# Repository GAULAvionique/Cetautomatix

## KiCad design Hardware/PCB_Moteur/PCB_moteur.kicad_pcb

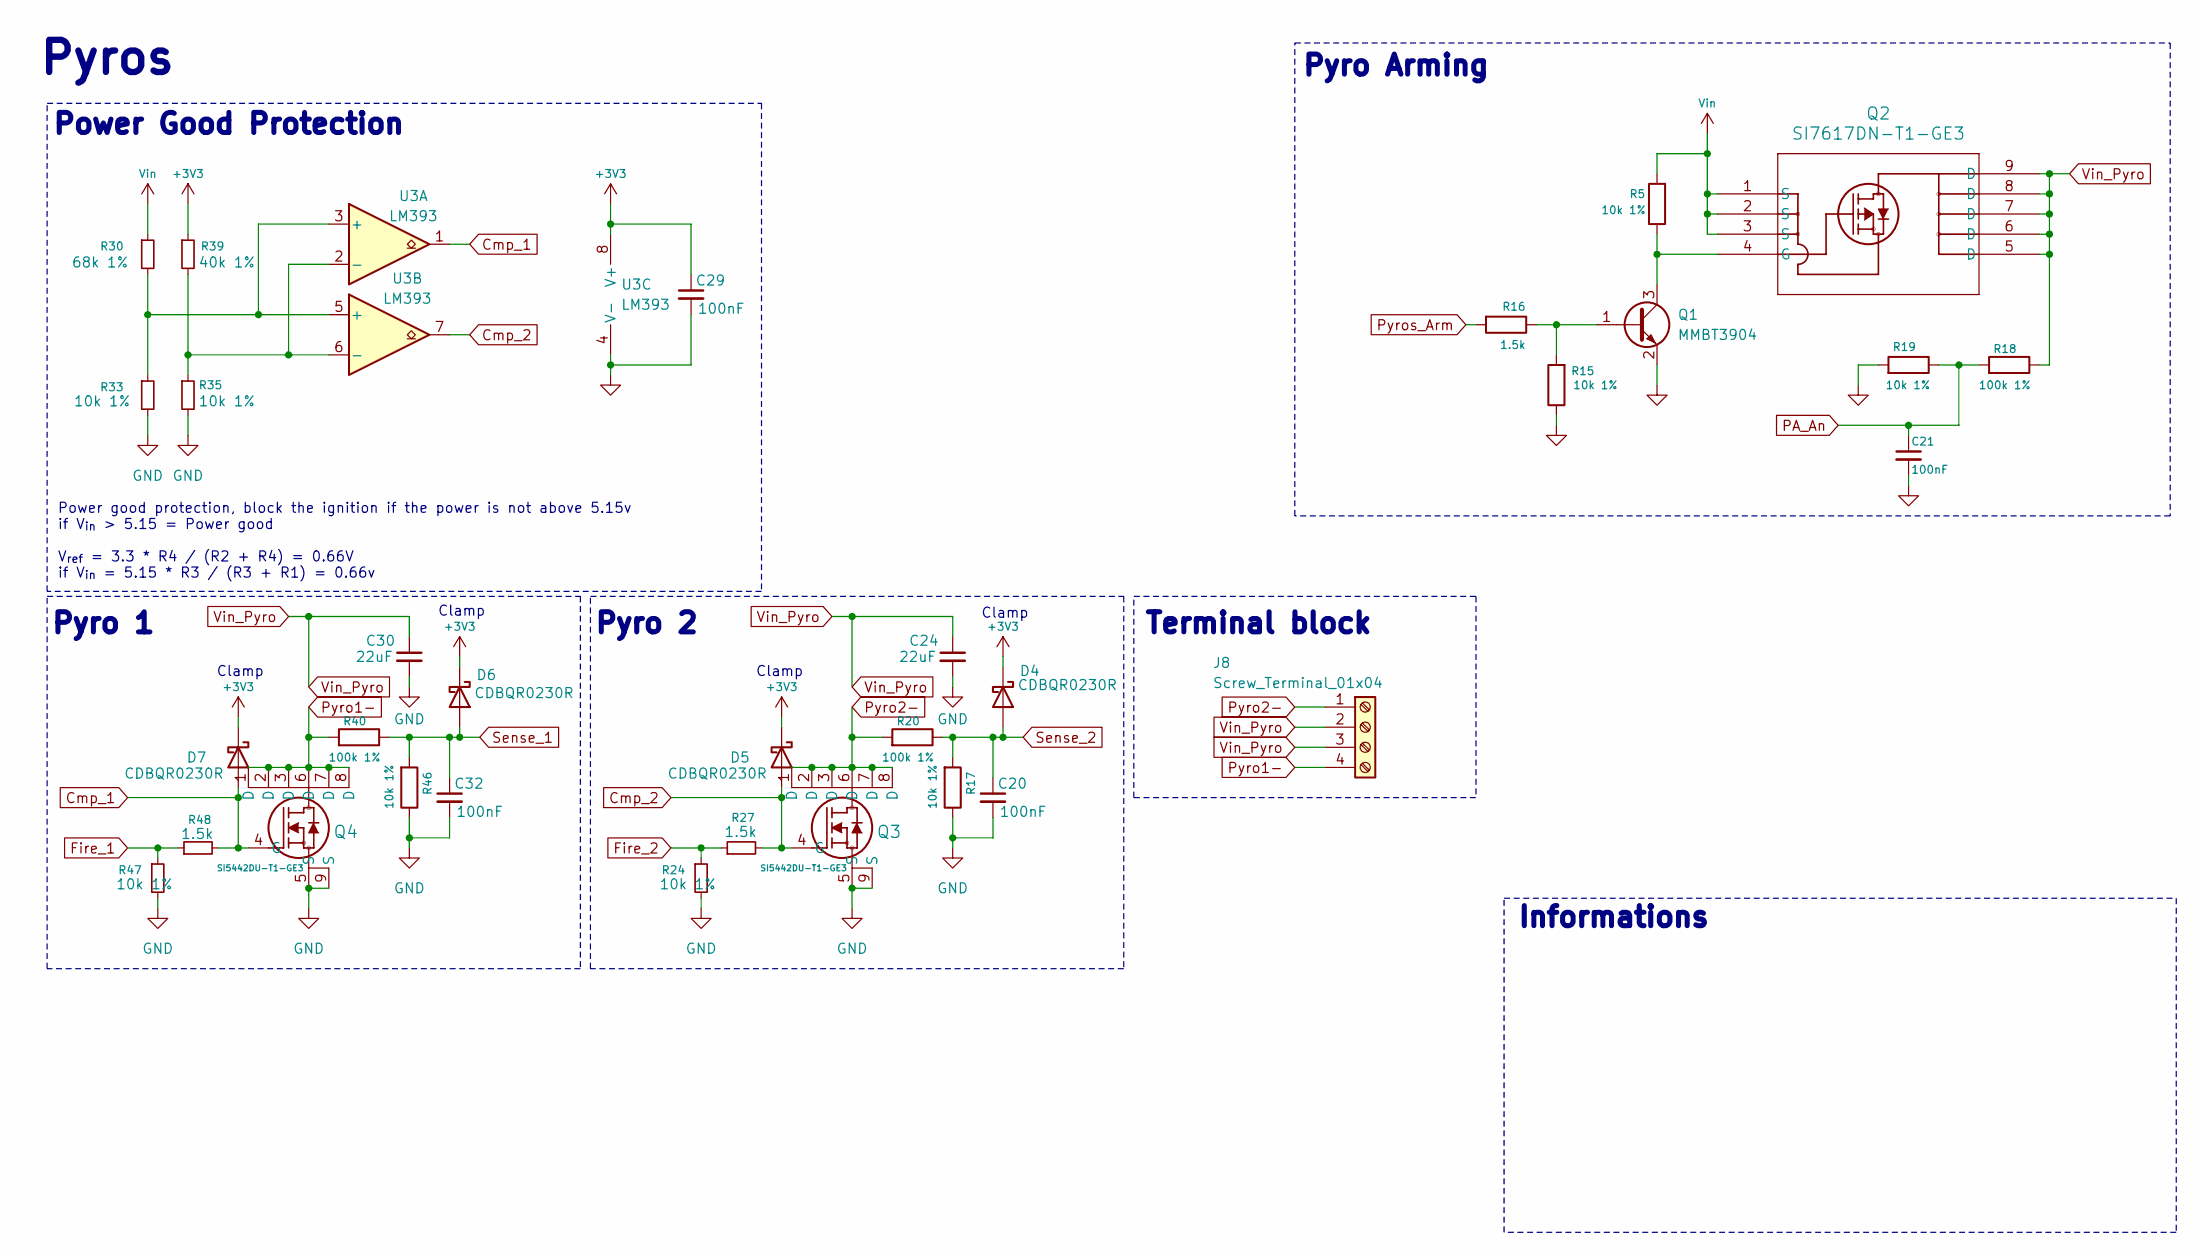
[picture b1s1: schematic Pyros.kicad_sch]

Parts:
C20, C21, C29, C32: 100nF; C_0805_2012Metric; Manufacturer_Part_Number C0805C104K5RACTU; DigiKey_Part_Number 399-C0805C104K5RACTUCT-ND
C24, C30: 22uF; C_0805_2012Metric; Manufacturer_Part_Number C2012X5R1V226M125AC; DigiKey_Part_Number 445-14428-1-ND
D4, D5, D6, D7: CDBQR0230R; D_0603_1608Metric; Manufacturer_Part_Number CD0603-B0340R; DigiKey_Part_Number CD0603-B0340RCT-ND
J8: Screw_Terminal_01x04; CONN_OSTVN04A150_OST; Manufacturer_Part_Number OSTVN04A150; DigiKey_Part_Number ED10563-ND
Q1: MMBT3904; SOT-23; Manufacturer_Part_Number MMBT3904LT1G; DigiKey_Part_Number MMBT3904LT1GOSCT-ND
Q2: SI7617DN-T1-GE3; POWERPAK_1212-8_VIS; Manufacturer_Part_Number SI7617DN-T1-GE3; DigiKey_Part_Number SI7617DN-T1-GE3CT-ND
Q3, Q4: SI5442DU-T1-GE3; SON_8DU-T1-GE3_VIS; Manufacturer_Part_Number SI5442DU-T1-GE3; DigiKey_Part_Number SI5442DU-T1-GE3CT-ND
R5, R15, R17, R19, R24, R33, R35, R46, R47: 10k 1%; R_0805_2012Metric; Manufacturer_Part_Number CRCW080510K0FKEA; DigiKey_Part_Number 541-10.0KCCT-ND
R16, R27, R48: 1.5k; R_0805_2012Metric; Manufacturer_Part_Number RC0805FR-071K5L; DigiKey_Part_Number 311-1.50KCRCT-ND
R18, R20, R40: 100k 1%; R_0805_2012Metric; Manufacturer_Part_Number RC0805FR-07100KL; DigiKey_Part_Number 311-100KCRCT-ND
R30: 68k 1%; R_0805_2012Metric; Manufacturer_Part_Number RMCF0805FT68K0; DigiKey_Part_Number RMCF0805FT68K0CT-ND
R39: 40k 1%; R_0805_2012Metric; Manufacturer_Part_Number CRCW080540K0FKEA; DigiKey_Part_Number 541-CRCW080540K0FKEACT-ND
U3: LM393; SOIC-8_3.9x4.9mm_P1.27mm; Manufacturer_Part_Number LM393DR; DigiKey_Part_Number 296-1015-1-ND

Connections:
3V3_Main: C29.1, D4.1 (K), D5.1 (K), D6.1 (K), D7.1 (K), R39.1, U3.8 (V+); also elsewhere on the board
Cmp_1: D7.2 (A), Q4.4 (G), R48.2, U3.1
Cmp_2: D5.2 (A), Q3.4 (G), R27.2, U3.7
Fire_1: R47.1, R48.1; also elsewhere on the board
Fire_2: R24.1, R27.1; also elsewhere on the board
GND: C20.2, C21.2, C24.2, C29.2, C30.2, C32.2, Q1.2 (E), Q3.5 (S), Q3.9 (S), Q4.5 (S), Q4.9 (S), R15.1, R17.1, R19.2, R24.2, R33.2, R35.2, R46.1, R47.2, U3.4 (V-); also elsewhere on the board
unnamed: Q1.1 (B), R15.2, R16.1
unnamed: Q1.3 (C), Q2.4 (G), R5.1
unnamed: R30.2, R33.1, U3.3 (+), U3.5 (+)
unnamed: R35.1, R39.2, U3.2 (-), U3.6 (-)
PA_An: C21.1, R18.2, R19.1; also elsewhere on the board
Pyro1-: J8.4, Q4.1 (D), Q4.2 (D), Q4.3 (D), Q4.6 (D), Q4.7 (D), Q4.8 (D), R40.2
Pyro2-: J8.1, Q3.1 (D), Q3.2 (D), Q3.3 (D), Q3.6 (D), Q3.7 (D), Q3.8 (D), R20.2
Pyros_Arm: R16.2; also elsewhere on the board
Sense_1: C32.1, D6.2 (A), R40.1, R46.2; also elsewhere on the board
Sense_2: C20.1, D4.2 (A), R17.2, R20.1; also elsewhere on the board
VIN_Filtered: Q2.1 (S), Q2.2 (S), Q2.3 (S), R5.2, R30.1; also elsewhere on the board
Vin_Pyro: C24.1, C30.1, J8.2, J8.3, Q2.5 (D), Q2.6 (D), Q2.7 (D), Q2.8 (D), Q2.9 (D), R18.1

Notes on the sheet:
Power good protection, block the ignition if the power is not above 5.15v if V_{in} > 5.15 = Power good V_{ref} = 3.3 * R4 / (R2 + R4) = 0.66V if V_{in} = 5.15 * R3 / (R3 + R1) = 0.66v
Clamp
Pyro 1
Terminal block
Pyro Arming
Pyros
Informations
Power Good Protection
Pyro 2

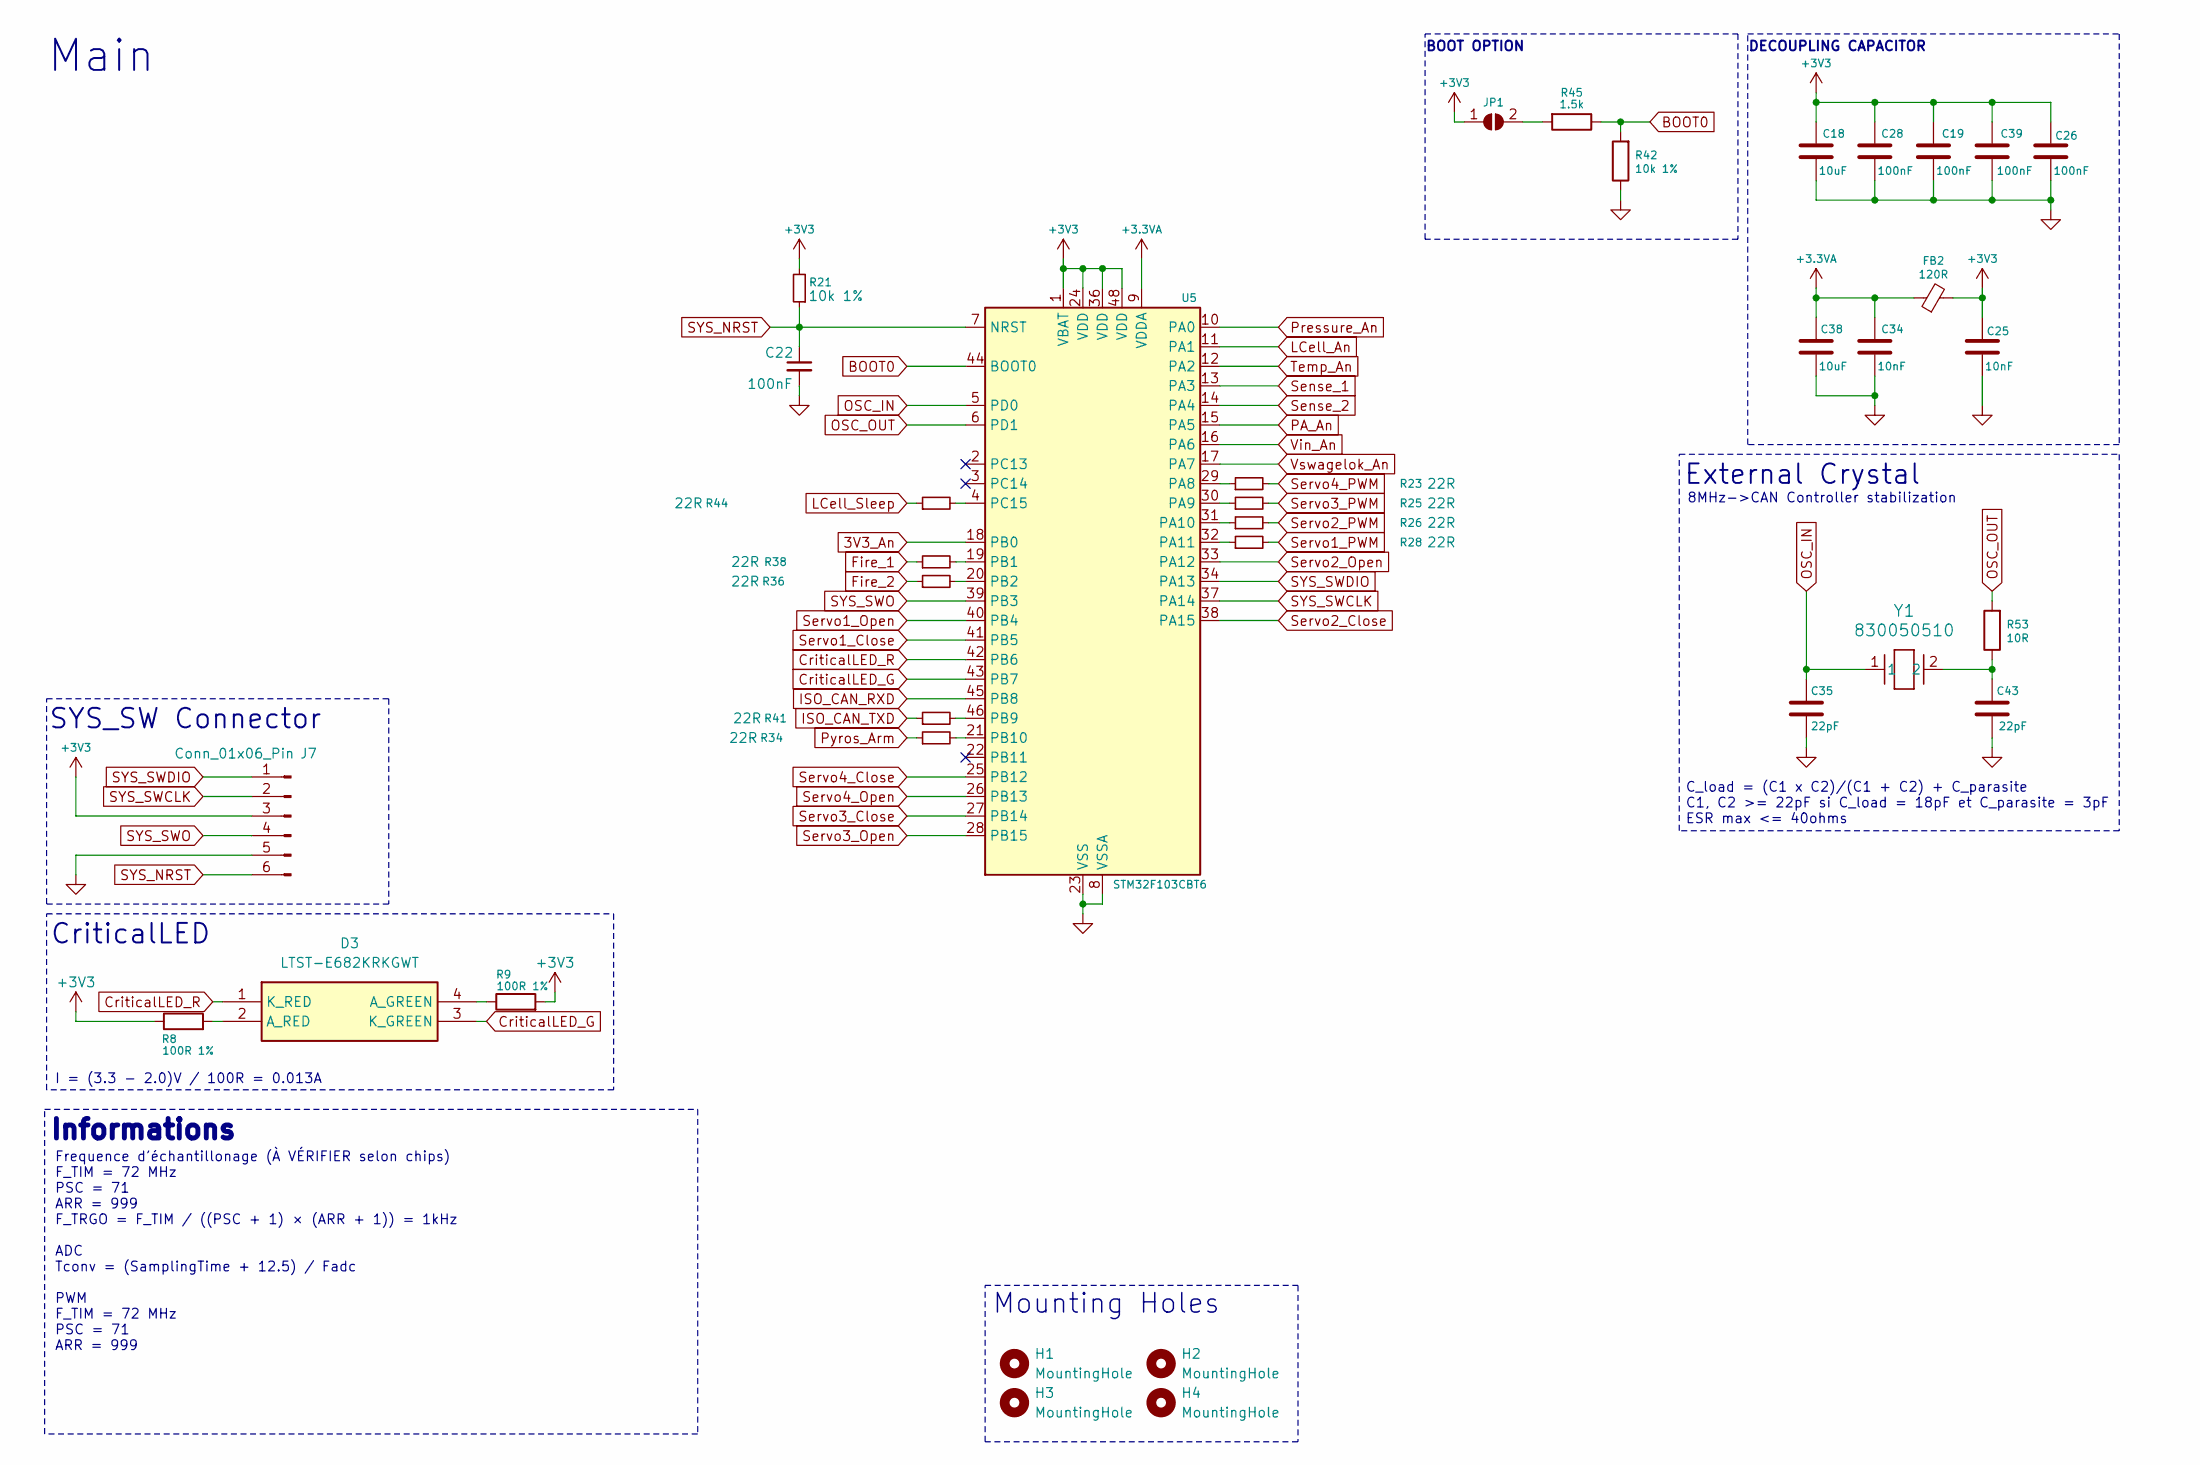
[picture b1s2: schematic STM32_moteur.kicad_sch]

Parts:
C18, C38: 10uF; C_0805_2012Metric; Manufacturer_Part_Number CL21A106KAYNNNE; DigiKey_Part_Number 1276-2891-1-ND
C19, C22, C26, C28, C39: 100nF; C_0805_2012Metric; Manufacturer_Part_Number C0805C104K5RACTU; DigiKey_Part_Number 399-C0805C104K5RACTUCT-ND
C25, C34: 10nF; C_0603_1608Metric; Manufacturer_Part_Number C0603C103K5RACTU; DigiKey_Part_Number 399-C0603C103K5RACTUCT-ND
C35, C43: 22pF; C_0805_2012Metric; Manufacturer_Part_Number QSCT251Q220F1GV001E; DigiKey_Part_Number 712-QSCT251Q220F1GV001ECT-ND
D3: LTST-E682KRKGWT; LTSTE683RGBW; Mouser Part Number 859-LTST-E682KRKGWT
FB2: 120R; L_0805_2012Metric; Manufacturer_Part_Number 2508051217Y6; DigiKey_Part_Number 1934-1472-1-ND
H1, H2, H3, H4: MountingHole; MountingHole_4.3mm_M4
J7: Conn_01x06_Pin; PinHeader_1x06_P2.54mm_Vertical; Manufacturer_Part_Number 61300611121; DigiKey_Part_Number 732-5319-ND
JP1: SolderJumper_2_Open; SolderJumper-2_P1.3mm_Open_TrianglePad1.0x1.5mm
R8, R9: 100R 1%; R_0805_2012Metric; Manufacturer_Part_Number YAG3360CT-ND; DigiKey_Part_Number RT0805FRE07100RL
R21, R42: 10k 1%; R_0805_2012Metric; Manufacturer_Part_Number CRCW080510K0FKEA; DigiKey_Part_Number 541-10.0KCCT-ND
R23, R25, R26, R28, R34, R36, R38, R41, R44: 22R; R_0603_1608Metric; Manufacturer_Part_Number ESR03EZPJ220; DigiKey_Part_Number RHM22DCT-ND
R45: 1.5k; R_0805_2012Metric; Manufacturer_Part_Number RC0805FR-071K5L; DigiKey_Part_Number 311-1.50KCRCT-ND
R53: 10R; R_0805_2012Metric; Manufacturer_Part_Number RC0805FR-0710RL; DigiKey_Part_Number 311-10.0CRCT-ND
U5: STM32F103CBT6; LQFP-48_7x7mm_P0.5mm; Manufacturer_Part_Number STM32F103CBT6; DigiKey_Part_Number 497-6288-ND
Y1: 830050510; Manufacturer_Part_Number 830050510; DigiKey_Part_Number 1923-830050510CT-ND

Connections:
3V3_An: U5.18 (PB0); also elsewhere on the board
3V3_Main: C18.2, C19.2, C25.2, C26.2, C28.2, C39.2, FB2.2, J7.3, JP1.1 (A), R8.1, R9.2, R21.2, U5.1 (VBAT), U5.24 (VDD), U5.36 (VDD), U5.48 (VDD); also elsewhere on the board
+3.3VA: C34.2, C38.2, FB2.1, U5.9 (VDDA)
BOOT0: R42.2, R45.1, U5.44 (BOOT0)
CriticalLED_G: D3.3 (K_GREEN), U5.43 (PB7)
CriticalLED_R: D3.1 (K_RED), U5.42 (PB6)
Fire_1: R38.1; also elsewhere on the board
Fire_2: R36.1; also elsewhere on the board
GND: C18.1, C19.1, C22.2, C25.1, C26.1, C28.1, C34.1, C35.1, C38.1, C39.1, C43.1, J7.5, R42.1, U5.8 (VSSA), U5.23 (VSS), U5.35 (VSS), U5.47 (VSS); also elsewhere on the board
ISO_CAN_RXD: U5.45 (PB8); also elsewhere on the board
ISO_CAN_TXD: R41.1; also elsewhere on the board
LCell_An: U5.11 (PA1); also elsewhere on the board
LCell_Sleep: R44.1; also elsewhere on the board
unnamed: C43.2, R53.1, Y1.2
unnamed: D3.4 (A_GREEN), R9.1
unnamed: D3.2 (A_RED), R8.2
unnamed: JP1.2 (B), R45.2
unnamed: R23.1, U5.29 (PA8)
unnamed: R25.1, U5.30 (PA9)
unnamed: R26.1, U5.31 (PA10)
unnamed: R28.1, U5.32 (PA11)
unnamed: R38.2, U5.19 (PB1)
unnamed: R36.2, U5.20 (PB2)
unnamed: R41.2, U5.46 (PB9)
unnamed: R34.2, U5.21 (PB10)
unnamed: R44.2, U5.4 (PC15)
OSC_IN: C35.2, U5.5 (PD0), Y1.1
OSC_OUT: R53.2, U5.6 (PD1)
PA_An: U5.15 (PA5); also elsewhere on the board
Pressure_An: U5.10 (PA0); also elsewhere on the board
Pyros_Arm: R34.1; also elsewhere on the board
SYS_NRST: C22.1, J7.6, R21.1, U5.7 (NRST)
SYS_SWCLK: J7.2, U5.37 (PA14)
SYS_SWDIO: J7.1, U5.34 (PA13)
SYS_SWO: J7.4, U5.39 (PB3)
Sense_1: U5.13 (PA3); also elsewhere on the board
Sense_2: U5.14 (PA4); also elsewhere on the board
Servo1_Close: U5.41 (PB5); also elsewhere on the board
Servo1_Open: U5.40 (PB4); also elsewhere on the board
Servo1_PWM: R28.2; also elsewhere on the board
Servo2_Close: U5.38 (PA15); also elsewhere on the board
Servo2_Open: U5.33 (PA12); also elsewhere on the board
Servo2_PWM: R26.2; also elsewhere on the board
Servo3_Close: U5.27 (PB14); also elsewhere on the board
Servo3_Open: U5.28 (PB15); also elsewhere on the board
Servo3_PWM: R25.2; also elsewhere on the board
Servo4_Close: U5.25 (PB12); also elsewhere on the board
Servo4_Open: U5.26 (PB13); also elsewhere on the board
Servo4_PWM: R23.2; also elsewhere on the board
Temp_An: U5.12 (PA2); also elsewhere on the board
Vin_An: U5.16 (PA6); also elsewhere on the board
Vswagelok_An: U5.17 (PA7); also elsewhere on the board

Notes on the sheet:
External Crystal
Mounting Holes
Main
BOOT OPTION
C_load = (C1 x C2)/(C1 + C2) + C_parasite C1, C2 >= 22pF si C_load = 18pF et C_parasite = 3pF ESR max <= 40ohms
DECOUPLING CAPACITOR
SYS_SW Connector
Informations
CriticalLED
I = (3.3 - 2.0)V / 100R = 0.013A
8MHz->CAN Controller stabilization
Frequence d'échantillonage (À VÉRIFIER selon chips) F_TIM = 72 MHz PSC = 71 ARR = 999 F_TRGO = F_TIM / ((PSC + 1) × (ARR + 1)) = 1kHz ADC Tconv = (SamplingTime + 12.5) / Fadc PWM F_TIM = 72 MHz PSC = 71 ARR = 999

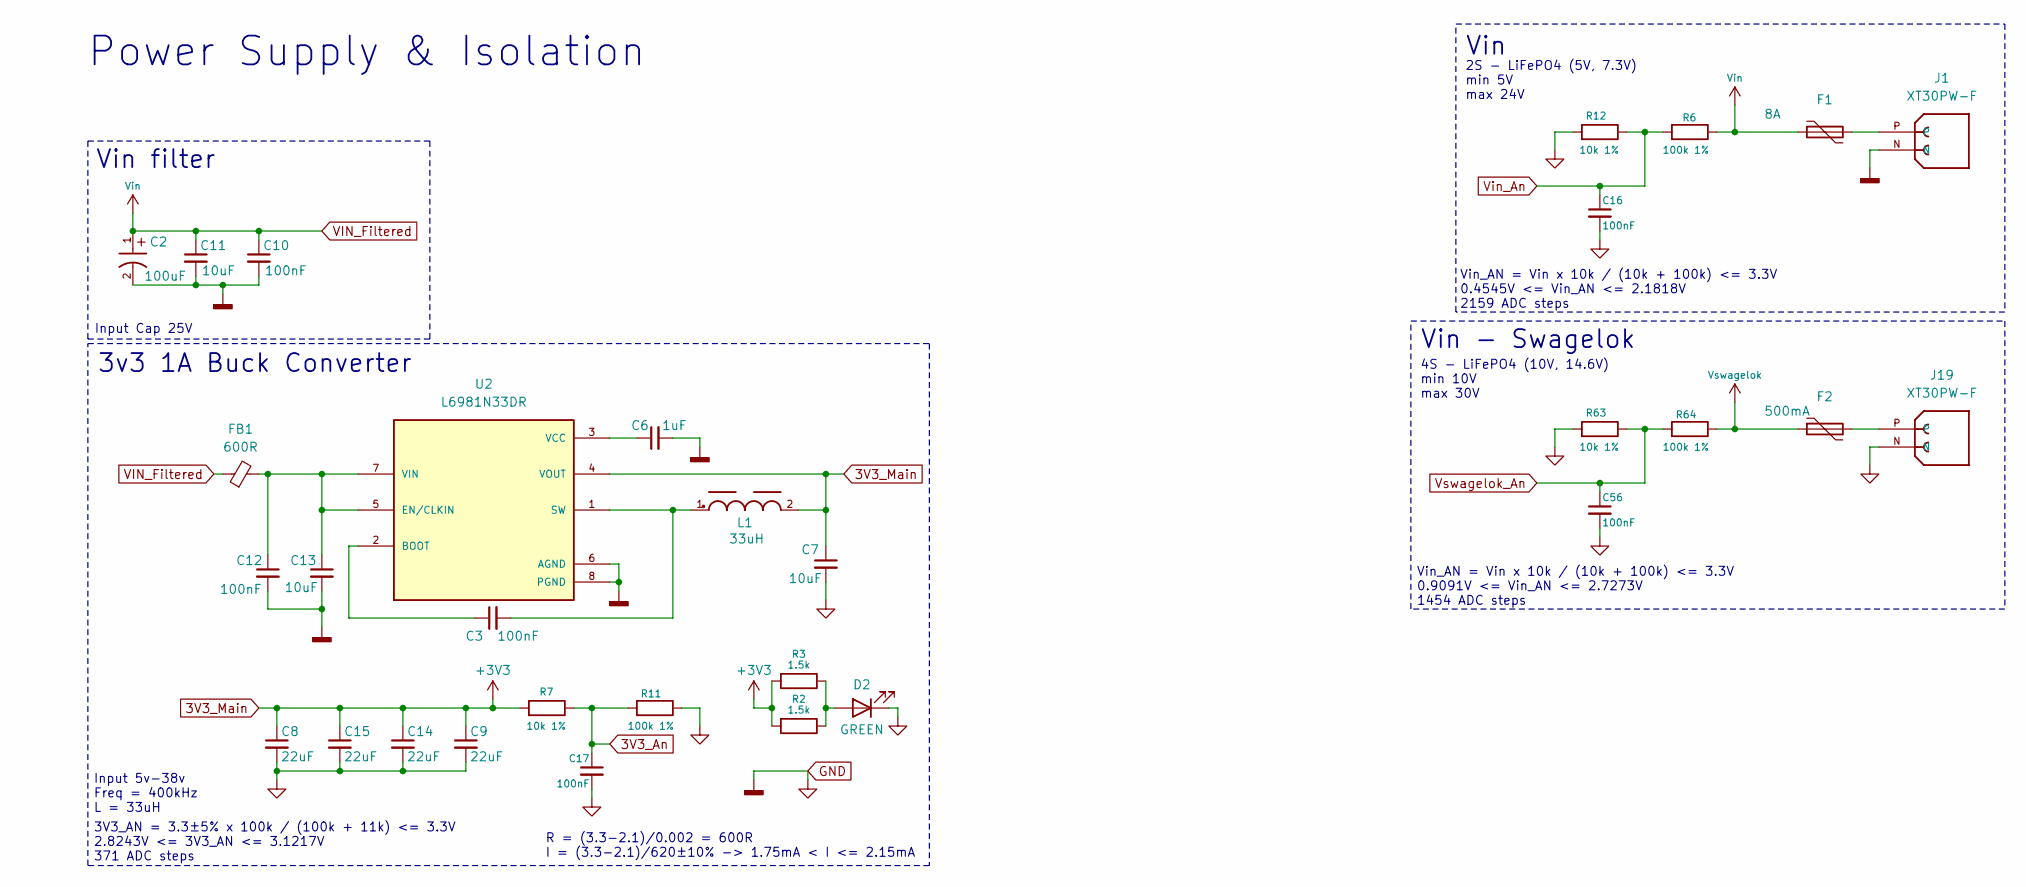
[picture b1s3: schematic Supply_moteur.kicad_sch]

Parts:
C2: 100uF; CP_Radial_D6.3mm_P2.50mm; Manufacturer_Part_Number 860040573004; DigiKey_Part_Number 732-9215-1-ND
C3, C10, C12, C16, C17, C56: 100nF; C_0805_2012Metric; Manufacturer_Part_Number C0805C104K5RACTU; DigiKey_Part_Number 399-C0805C104K5RACTUCT-ND
C6: 1uF; C_0805_2012Metric; Manufacturer_Part_Number CL21B105KBFNNNE; DigiKey_Part_Number 1276-1029-1-ND
C7, C11, C13: 10uF; C_0805_2012Metric; Manufacturer_Part_Number CL21A106KAYNNNE; DigiKey_Part_Number 1276-2891-1-ND
C8, C9, C14, C15: 22uF; C_0805_2012Metric; Manufacturer_Part_Number C2012X5R1V226M125AC; DigiKey_Part_Number 445-14428-1-ND
D2: GREEN; LED_QBLP601-AG15; Manufacturer_Part_Number QBLP601-AG15; DigiKey_Part_Number 1516-QBLP601-AG15CT-ND
F1: 8A; Fuse_2920_7451Metric; Manufacturer_Part_Number 2920L400/15MR; DigiKey_Part_Number F8136CT-ND
F2: 500mA; Fuse_0805_2012Metric; Manufacturer_Part_Number 0805L020/24YR; DigiKey_Part_Number 18-0805L020/24YRCT-ND
FB1: 600R; L_1210_3225Metric; Manufacturer_Part_Number FBMH3225HM601NT; DigiKey_Part_Number 587-1755-1-ND
J1, J19: XT30PW-F; PARTREV 1.2
L1: 33uH; WE-PD_1245; Manufacturer_Part_Number 7447715330; DigiKey_Part_Number 732-2196-1-ND
R2, R3: 1.5k; R_0805_2012Metric; Manufacturer_Part_Number RC0805FR-071K5L; DigiKey_Part_Number 311-1.50KCRCT-ND
R6, R11, R64: 100k 1%; R_0805_2012Metric; Manufacturer_Part_Number RC0805FR-07100KL; DigiKey_Part_Number 311-100KCRCT-ND
R7, R12, R63: 10k 1%; R_0805_2012Metric; Manufacturer_Part_Number CRCW080510K0FKEA; DigiKey_Part_Number 541-10.0KCCT-ND
U2: L6981N33DR; PARTREV 3; DigiKey_Part_Number 497-L6981N33DRCT-ND

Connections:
3V3_An: C17.1, R7.1, R11.2; also elsewhere on the board
3V3_Main: C7.1, C8.1, C9.1, C14.1, C15.1, L1.2, R2.2, R3.2, R7.2, U2.4 (VOUT); also elsewhere on the board
GND: C2.2, C6.2, C7.2, C8.2, C9.2, C10.2, C11.2, C12.2, C13.2, C14.2, C15.2, C16.2, C17.2, C56.2, D2.1 (K), J1.N, J19.N, R11.1, R12.2, R63.2, U2.6 (AGND), U2.8 (PGND); also elsewhere on the board
unnamed: D2.2 (A), R2.1, R3.1
unnamed: F1.2, J1.P
unnamed: F2.2, J19.P
unnamed: C3.1, U2.2 (BOOT)
unnamed: C12.1, C13.1, FB1.2, U2.5 (EN/CLKIN), U2.7 (VIN)
unnamed: C3.2, L1.1, U2.1 (SW)
unnamed: C6.1, U2.3 (VCC)
VIN_Filtered: C2.1, C10.1, C11.1, F1.1, FB1.1, R6.1; also elsewhere on the board
Vin_An: C16.1, R6.2, R12.1; also elsewhere on the board
Vswagelok: F2.1, R64.1; also elsewhere on the board
Vswagelok_An: C56.1, R63.1, R64.2; also elsewhere on the board

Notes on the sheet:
Vin_AN = Vin x 10k / (10k + 100k) <= 3.3V 0.4545V <= Vin_AN <= 2.1818V 2159 ADC steps
Vin - Swagelok
Input 5v-38v Freq = 400kHz L = 33uH
Vin_AN = Vin x 10k / (10k + 100k) <= 3.3V 0.9091V <= Vin_AN <= 2.7273V 1454 ADC steps
R = (3.3-2.1)/0.002 = 600R I = (3.3-2.1)/620±10% -> 1.75mA < I <= 2.15mA
Power Supply & Isolation
Vin
Vin filter
2S - LiFePO4 (5V, 7.3V) min 5V max 24V
Input Cap 25V
4S - LiFePO4 (10V, 14.6V) min 10V max 30V
3V3_AN = 3.3±5% x 100k / (100k + 11k) <= 3.3V 2.8243V <= 3V3_AN <= 3.1217V 371 ADC steps
3v3 1A Buck Converter

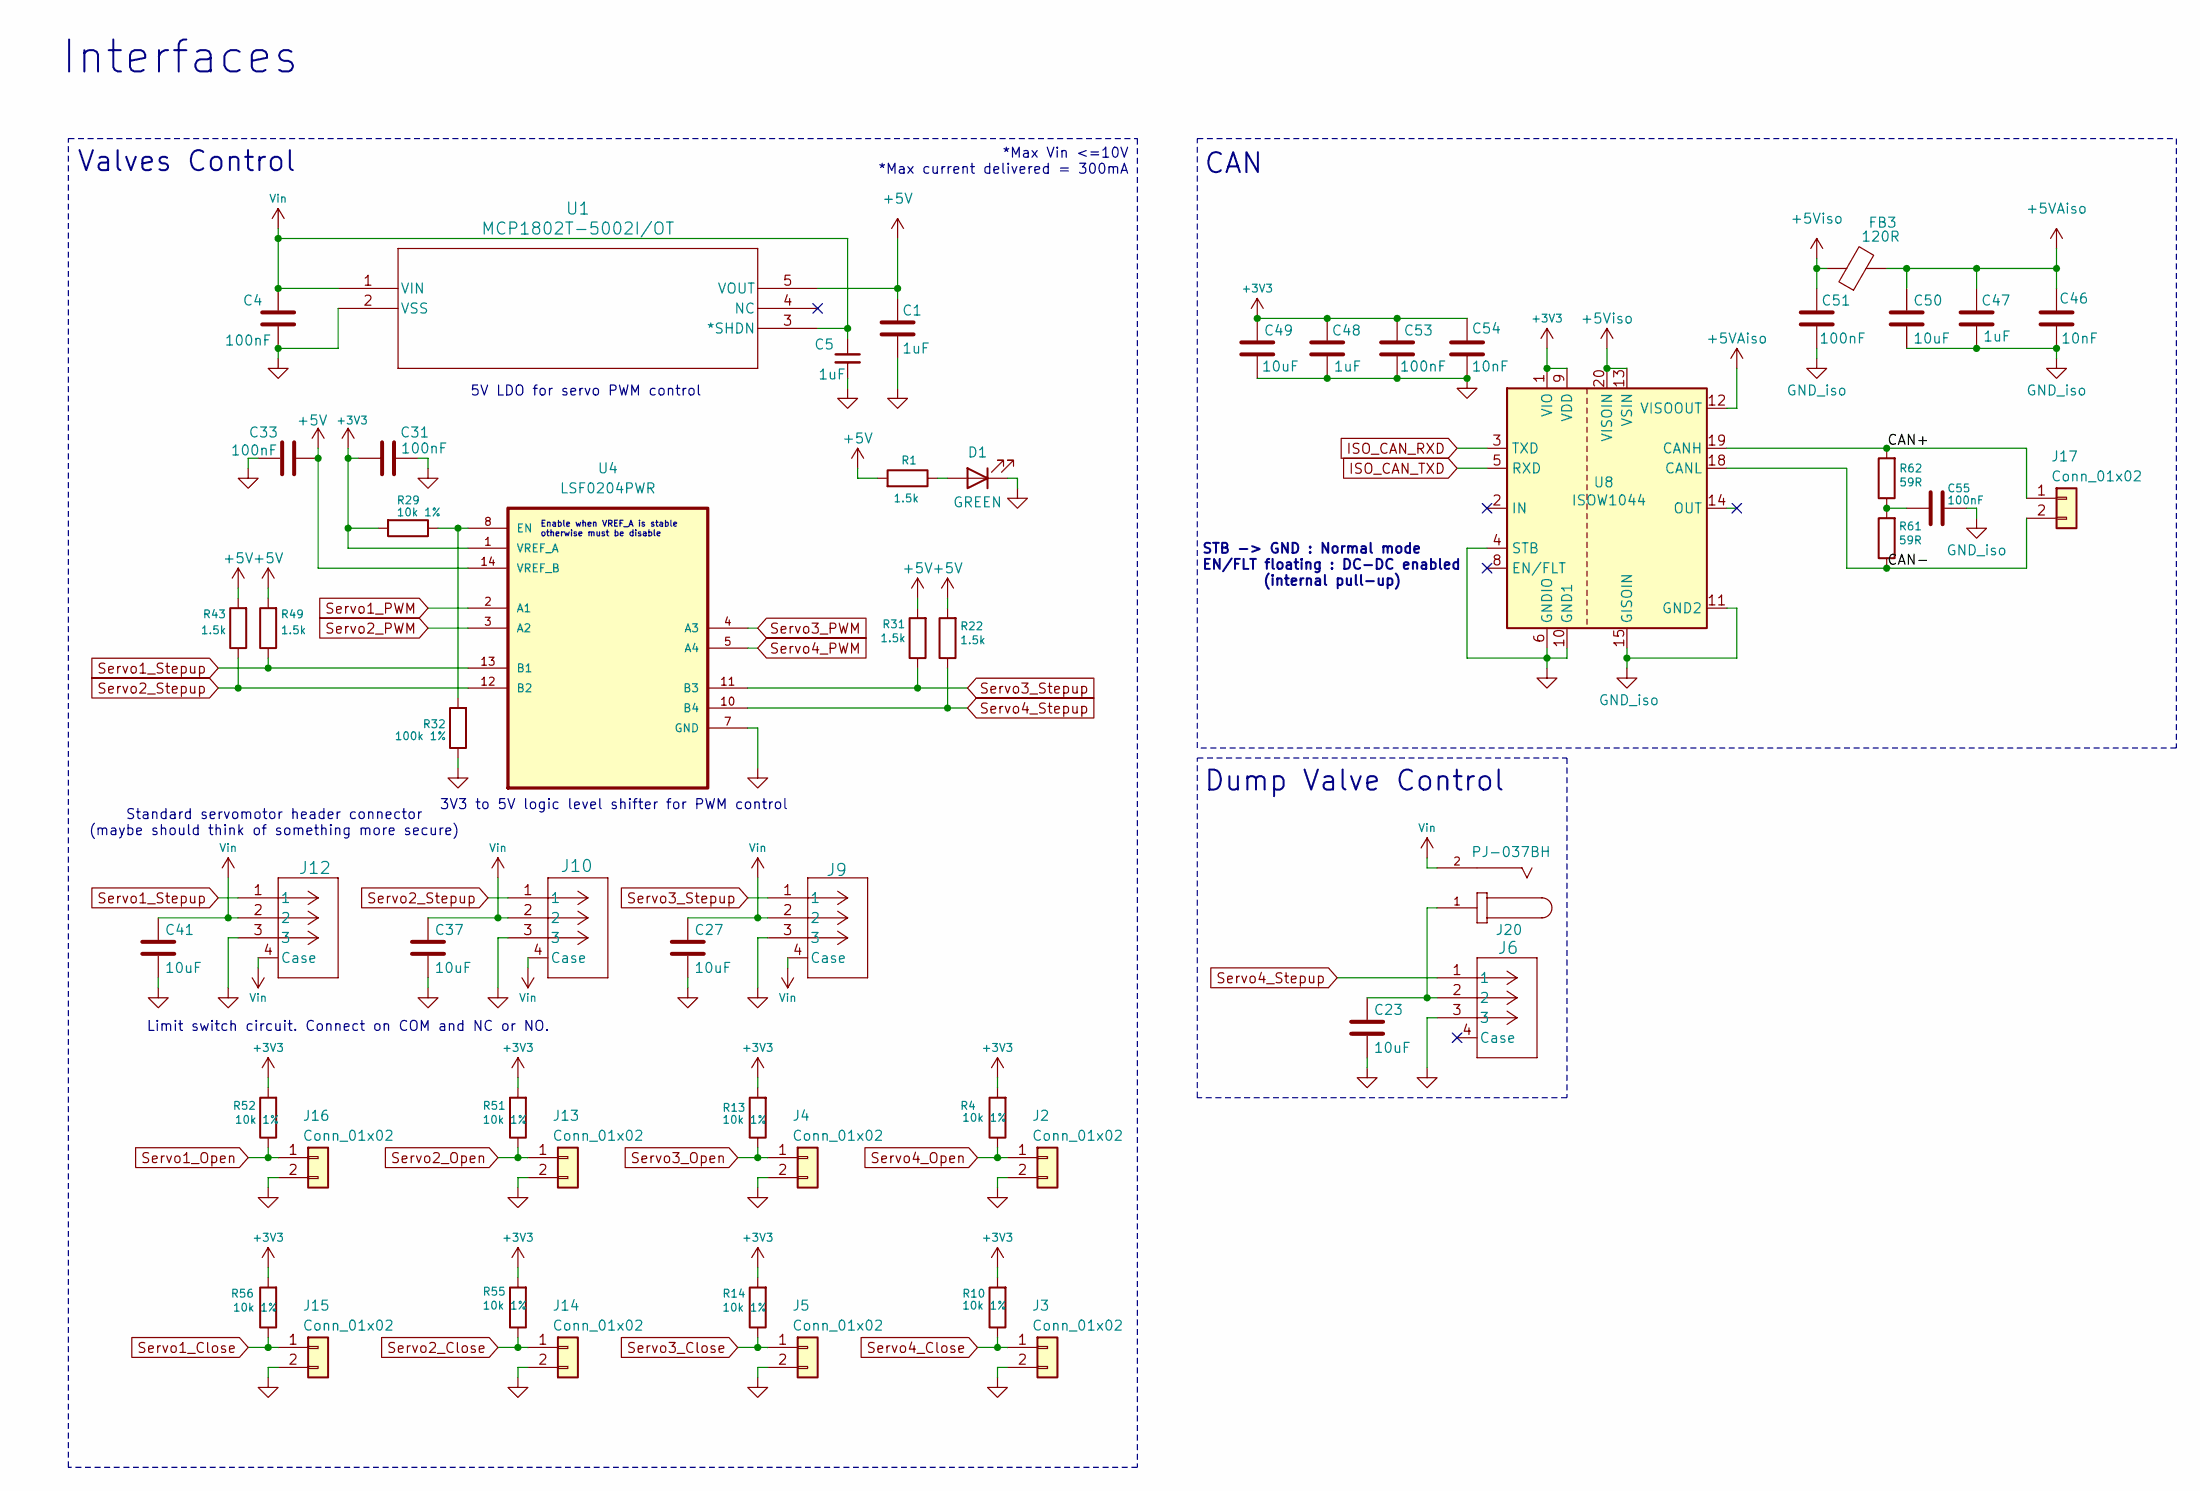
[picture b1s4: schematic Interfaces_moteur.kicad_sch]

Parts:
C1, C5, C47, C48: 1uF; C_0805_2012Metric; Manufacturer_Part_Number CL21B105KBFNNNE; DigiKey_Part_Number 1276-1029-1-ND
C4, C31, C33, C51, C53, C55: 100nF; C_0805_2012Metric; Manufacturer_Part_Number C0805C104K5RACTU; DigiKey_Part_Number 399-C0805C104K5RACTUCT-ND
C23, C27, C37, C41, C49, C50: 10uF; C_0805_2012Metric; Manufacturer_Part_Number CL21A106KAYNNNE; DigiKey_Part_Number 1276-2891-1-ND
C46, C54: 10nF; C_0603_1608Metric; Manufacturer_Part_Number C0603C103K5RACTU; DigiKey_Part_Number 399-C0603C103K5RACTUCT-ND
D1: GREEN; LED_QBLP601-AG15; Manufacturer_Part_Number QBLP601-AG15; DigiKey_Part_Number 1516-QBLP601-AG15CT-ND
FB3: 120R; L_0805_2012Metric; Manufacturer_Part_Number 2508051217Y6; DigiKey_Part_Number 1934-1472-1-ND
J2, J3, J4, J5, J13, J14, J15, J16: Conn_01x02; TE_640454-2; Manufacturer_Part_Number 640454-2; DigiKey_Part_Number A19423-ND
J6, J9, J10, J12: SM03B-GHS-TB; JST_SM03B-GHS-TB; Manufacturer_Part_Number SM03B-GHS-TB; DigiKey_Part_Number 455-SM03B-GHS-TBCT-ND
J17: Conn_01x02; CONN_2189890010-SD_02_MOL; Manufacturer_Part_Number 2189890210; DigiKey_Part_Number 900-2189890210CT-ND
J20: PJ-037BH; SAMESKY_PJ-037BH; PARTREV 1.08; DigiKey_Part_Number CP-037BH-ND
R1, R22, R31, R43, R49: 1.5k; R_0805_2012Metric; Manufacturer_Part_Number RC0805FR-071K5L; DigiKey_Part_Number 311-1.50KCRCT-ND
R4, R10, R13, R14, R29, R51, R52, R55, R56: 10k 1%; R_0805_2012Metric; Manufacturer_Part_Number CRCW080510K0FKEA; DigiKey_Part_Number 541-10.0KCCT-ND
R32: 100k 1%; R_0805_2012Metric; Manufacturer_Part_Number RC0805FR-07100KL; DigiKey_Part_Number 311-100KCRCT-ND
R61, R62: 59R; R_0805_2012Metric; Manufacturer_Part_Number RC0805FR-0759RL; DigiKey_Part_Number 311-59.0CRCT-ND
U1: MCP1802T-5002I/OT; MCP1802T-5002IOT; Manufacturer_Part_Number MCP1802T-5002I/OT; DigiKey_Part_Number MCP1802T-5002I/OTCT-ND
U4: LSF0204PWR; TSSOP-14_4.4x5mm_P0.65mm; Manufacturer_Part_Number LSF0204PWR; DigiKey_Part_Number 296-LSF0204PWRCT-ND
U8: ISOW1044; SOIC-20W_7.5x12.8mm_P1.27mm; Manufacturer_Part_Number ISOW1044BDFMR; DigiKey_Part_Number 296-ISOW1044BDFMRCT-ND

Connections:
3V3_Main: C31.1, C48.1, C49.1, C53.1, C54.1, R4.2, R10.2, R13.2, R14.2, R29.2, R51.2, R52.2, R55.2, R56.2, U4.1 (VREF_A), U8.1 (VIO), U8.9 (VDD); also elsewhere on the board
+5V: C1.1, C33.1, R1.2, R22.2, R31.2, R43.2, R49.2, U1.5 (VOUT), U4.14 (VREF_B)
+5VAiso: C46.1, C47.1, C50.1, FB3.2, U8.12 (VISOOUT)
+5Viso: C51.1, FB3.1, U8.13 (VSIN), U8.20 (VISOIN)
/Interfaces/CAN+: J17.1, R62.2, U8.19 (CANH)
/Interfaces/CAN-: J17.2, R61.1, U8.18 (CANL)
GND: C1.2, C4.2, C5.2, C23.2, C27.2, C31.2, C33.2, C37.2, C41.2, C48.2, C49.2, C53.2, C54.2, D1.1 (K), J2.2, J3.2, J4.2, J5.2, J6.3, J9.3, J10.3, J12.3, J13.2, J14.2, J15.2, J16.2, R32.1, U1.2 (VSS), U4.7 (GND), U8.4 (STB), U8.6 (GNDIO), U8.10 (GND1); also elsewhere on the board
GND_iso: C46.2, C47.2, C50.2, C51.2, C55.2, U8.11 (GND2), U8.15 (GISOIN), U8.16 (GISOIN), U8.17 (GISOIN)
ISO_CAN_RXD: U8.3 (TXD); also elsewhere on the board
ISO_CAN_TXD: U8.5 (RXD); also elsewhere on the board
unnamed: C23.1, J6.2, J20.1
unnamed: C55.1, R61.2, R62.1
unnamed: D1.2 (A), R1.1
unnamed: R29.1, R32.2, U4.8 (EN)
Servo1_Close: J15.1, R56.1; also elsewhere on the board
Servo1_Open: J16.1, R52.1; also elsewhere on the board
Servo1_PWM: U4.2 (A1); also elsewhere on the board
Servo1_Stepup: J12.1, R49.1, U4.13 (B1)
Servo2_Close: J14.1, R55.1; also elsewhere on the board
Servo2_Open: J13.1, R51.1; also elsewhere on the board
Servo2_PWM: U4.3 (A2); also elsewhere on the board
Servo2_Stepup: J10.1, R43.1, U4.12 (B2)
Servo3_Close: J5.1, R14.1; also elsewhere on the board
Servo3_Open: J4.1, R13.1; also elsewhere on the board
Servo3_PWM: U4.4 (A3); also elsewhere on the board
Servo3_Stepup: J9.1, R31.1, U4.11 (B3)
Servo4_Close: J3.1, R10.1; also elsewhere on the board
Servo4_Open: J2.1, R4.1; also elsewhere on the board
Servo4_PWM: U4.5 (A4); also elsewhere on the board
Servo4_Stepup: J6.1, R22.1, U4.10 (B4)
VIN_Filtered: C4.1, C5.1, C27.1, C37.1, C41.1, J9.2, J9.4 (Case), J10.2, J10.4 (Case), J12.2, J12.4 (Case), J20.2, U1.1 (VIN), U1.3 (*SHDN); also elsewhere on the board

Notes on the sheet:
Valves Control
CAN
STB -> GND : Normal mode EN/FLT floating : DC-DC enabled (internal pull-up)
*Max Vin <=10V *Max current delivered = 300mA
5V LDO for servo PWM control
3V3 to 5V logic level shifter for PWM control
Dump Valve Control
Standard servomotor header connector (maybe should think of something more secure)
Interfaces
Limit switch circuit. Connect on COM and NC or NO.
Enable when VREF_A is stable otherwise must be disable
